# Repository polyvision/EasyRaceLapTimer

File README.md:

# EasyRaceLapTimer

EasyRaceLapTimer is a complete open source lap time tracker all-in-one solution for FPV racing quads. It supports an infrared based tracker solution which is completly open hardware and a VTX solution

What you get with EasyRaceLapTimer:

**Features:**

* host system for tracking the laps
* VTX sensoring
* IR transponders (code & schematic files for building them) with a transmitting range of 2 to 4 meters
* 63 available transponder IDs when using the project transponders
* changing the ID via a push button on the transponder, no additional programming required (started with version 0.3.1 of the transponders)
* update transponders with new code (Arduino hardware needed)
* setup guide for building your Raspberry PI host station
* the host station is also a WiFi access point to change configs etc on the fly
* monitoring mode, you can watch the stats with your mobile phones
* add your own team logo to the monitoring mode
* detailed stats about pilots and races
* sound effects for various events in a race
* TCP/IP and serial connections support for receiving lap times and commands from other time tracking systems
* export race events to PDF
* standard practice/ time trial mode
* competition mode for racing events with time penalties (satellites needed)
* automatic restarting of a race session after a specified idle time
* complete race management with heats & groups
* and much more comming soon

**Important notices**

EasyRaceLapTimer works basicly with any IR transponder, as long as you provide code for interpreting the IR pulses. Just have a look at the *ir_daemon* tool.

Be sure to use the full size of your SD card on the Raspberry PI

    sudo raspi-config

# Important information

The documentation for the project can be found in the [/docs](https://github.com/polyvision/EasyRaceLapTimer/tree/master/docs) directory.
There's also a huge [RCGroups](http://www.rcgroups.com/forums/showthread.php?t=2538917) thread with lots of answered questions, images etc.

# Version 0.6.x

You can download a SD card image for the PI of EasyRaceLapTimer on the following pages:

http://www.airbirds.de
http://www.easyracelaptimer.com

There's also an introduction video to the system.

# file structure

**/docs**
  documentation of nearly every part of the package

**/web**

the rails application

**/Arduino**

all arduino sketches

**/ir_daemon**

the cpp daemon for receiving the IR pulses

**/datasheets**

schematic files and more for transponders etc.

# Installation

fetch the source via git with the following command

    git clone git@github.com:polyvision/EasyRaceLapTimer.git

more details of each indivial package can be found in the *docs* folder

# Contributors
 * [Peter Provost](https://github.com/PProvost)
 * [Peisel](https://github.com/peisel)
 * [p3root](https://github.com/p3root)
 * [Sven Michel](https://github.com/svenmichel)
 * [bilson](https://github.com/bilson)
 
 and many more ! just add yourself if you contributed!

# license

The complete project uses the [GPL V3 license](http://www.gnu.org/licenses/gpl-3.0.de.html)

**development and sponsoring by [AirBirds](http://www.airbirds.de)**

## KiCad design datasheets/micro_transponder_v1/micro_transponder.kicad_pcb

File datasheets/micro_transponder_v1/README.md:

This is a transponder intended for indoor microdrones. It's not that bright, 
which is fine when flying only a few feet from the receiver. It's also very 
small, which is good when every milligram counts.

It can still be programmed using alligator clips on the sides. The lettering 
on the back will show you which pad goes where (PB0, PB1, etc.). See the 
ATtiny85 datasheet for how they connect to the physical pins and their 
extended features.

Solder the +5V and GND pads to the power. If necessary, a +3.7V input (such as 
from a 1S lipo cell) should be enough.

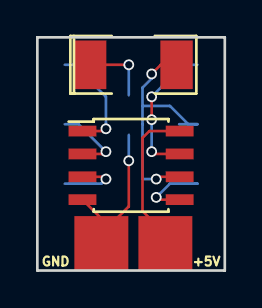
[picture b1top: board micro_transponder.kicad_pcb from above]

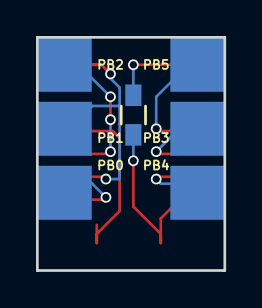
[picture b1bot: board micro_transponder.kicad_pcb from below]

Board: 2 copper layers, 10.4 x 13.0 mm, 9 parts (7 on the bottom side), 8 nets.

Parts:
D1: LED; SMD-2010_Pol
IC1: ATTINY85-S; SOIC-8_3.9x4.9mm_Pitch1.27mm
P1, P2, P3, P4, P5, P6: CONN_01X01; Measurement_Point_Square-SMD-Pad_Big
R1: 150 Ohm, 0.25W; R_0603_HandSoldering

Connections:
GND: IC1.4, R1.2
unnamed: D1.1, R1.1
unnamed: D1.2, IC1.6, P2.1
unnamed: IC1.1, P6.1
unnamed: IC1.2, P4.1
unnamed: IC1.3, P5.1
unnamed: IC1.5, P1.1
unnamed: IC1.7, P3.1

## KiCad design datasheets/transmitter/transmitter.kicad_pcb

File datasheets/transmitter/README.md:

**IMPORTANT**: This circuit changes the ATtiny85 output to pin 2, instead of pin 6. Be sure 
to change the program accordingly.  This makes room for the AVR ISP to attach without any 
overlapping pins.

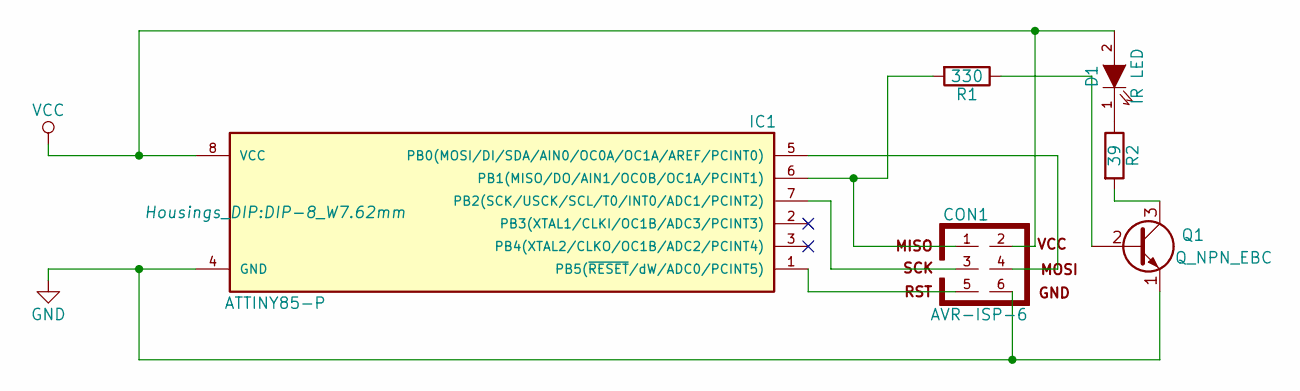
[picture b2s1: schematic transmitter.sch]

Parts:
CON1: AVR-ISP-6; Pin_Header_Straight_2x03
D1: IR LED; Pin_Header_Straight_1x02
IC1: ATTINY85-P; DIP-8_W7.62mm
Q1: Q_NPN_EBC; TO-92_Inline_Narrow_Oval
R1: 330; Resistor_Horizontal_RM7mm
R2: 39; Resistor_Horizontal_RM7mm

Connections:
GND: CON1.6, IC1.4 (GND), Q1.1 (E)
unnamed: CON1.1, IC1.6 (PB1(MISO/DO/AIN1/OC0B/OC1A/PCINT1)), R1.2
unnamed: CON1.3, IC1.7 (PB2(SCK/USCK/SCL/T0/INT0/ADC1/PCINT2))
unnamed: CON1.4, IC1.5 (PB0(MOSI/DI/SDA/AIN0/OC0A/OC1A/AREF/PCI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)
unnamed: CON1.5, IC1.1 (PB5(~RESET~/dW/ADC0/PCINT5))
unnamed: D1.1 (K), R2.1
unnamed: Q1.2 (B), R1.1
unnamed: Q1.3 (C), R2.2
VCC: CON1.2, D1.2 (A), IC1.8 (VCC)

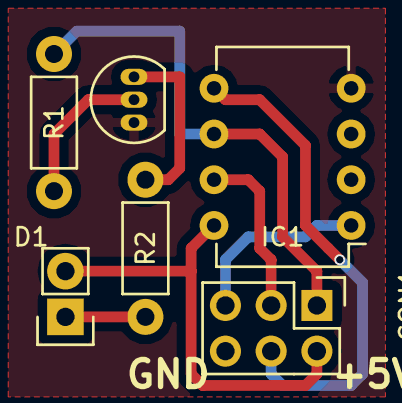
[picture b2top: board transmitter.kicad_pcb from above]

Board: 2 copper layers, 6 parts (0 on the bottom side), 9 nets.

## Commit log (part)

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2015-11-03 first working version of receiver
2015-11-04 new file strucure
2015-11-04 added some docs
2015-11-06 updated docs
2015-11-08 3 sensor support added buzzer support
2015-11-08 added gpio wiring for raspberry2
2015-11-09 added hardware.md
2015-11-10 added missing part
2015-11-13 added database config for production mode
2015-11-13 added pilots views, bugfixes
2015-11-13 fixes
2015-11-13 websockets r now configurable via env variable RAILS_CABLE_IP
2015-11-13 added init.d script
2015-11-14 added new style, added check for too fast lap
2015-11-16 preparing first stable release
2015-11-17 changed ir_daemon to 9 bit mode POST requests in seperate threads
2015-11-17 added Arduino files for the new 9bit transponder docs updated etc
2015-11-18 added missing transponder setup file
2015-11-18 added blog post link
2015-11-19 added soundfile configuration
2015-11-19 changed checksum calculation according to the documentation
2015-11-19 changed checksum calculation -> added new Transponder code v0.2
2015-11-20 better documentation
2015-11-20 updated documentation
2015-11-20 fixed a bug in displaying last rounds wrong time
2015-11-23 added api testing new config value lap_max_lap_time_in_seconds
2015-11-23 added database cleaner gem
2015-11-23 added button support on PIN 14 to start a new race started to clean up ir_daemon code
2015-11-24 rewrite of ir_daemon to support additionaly TCP/IP and serial connections
2015-11-24 Update setup_guide.md
    Made a bunch of edits and clarifications to help new users.
2015-11-26 added file
2015-11-27 better ui
2015-11-27 upcomming v0.3 added sensor case for different direction started to write update instructions, not complete yet
2015-11-30 wip competition mode
2015-12-01 first working version of the competition mode
2015-12-02 displayotron 3000 HAT server
2015-12-02 added lcd support (Displayotron 3000 HAT) support by adding an info server added more config switches to the ir_daemon
2015-12-04 beginning of satellite mode and time penalties for competition mode
2015-12-06 fixed competition mode ranking beginning of pdf generation
2015-12-06 add arch-linux description
2015-12-07 fixed a bug with double using transponder tokens
2015-12-07 satellite mode for the ir_daemon
2015-12-08 various bug fixes
2015-12-10 added version info the gui fixex image bug in pdf export
2015-12-10 - refactoring - added logging class for syslog and console logging (file is todo) - possibility to add more ir sensors via config file
2015-12-10 removed readme file
2015-12-10 updated testing code for Arduino Nano
2015-12-18 monitor view updates all 2 seconds removed actioncable
2015-12-18 changed config values
2015-12-18 first implementation of hot seat mode
2015-12-19 fixed spelling
2015-12-19 fixed a bug regarding hot seat mode in competition mode added spec for hot seat mode
2015-12-21 added udp broadcast, first tests
2015-12-22 fixes for upcomming v0.4b2
2015-12-22 fix for button visibility
2015-12-22 button visibility
2015-12-23 fixed typos and updated docs
2015-12-24 personal best lap time sfx
2015-12-24 fix for resetting the ir_daemon
2015-12-25 added sidekiq for background processing
2015-12-25 Use existing INI file and settings if exists
2016-01-04 test
2016-01-05 new colors new feeling more racy
2016-01-06 css fix
2016-01-11 working volume control
2016-01-11 playing custom sound files from via race director
2016-01-17 first working version of race director in the web gui improved some things and fixed a couple of bugs in ir_daemon
2016-01-17 fixes regarding logging
2016-01-22 fixed bug with creating a race session
2016-01-26 wip...
2016-01-29 play sound files for each lap in competition mode
2016-01-30 working playing lap num sound for a pilot in standard racing mode
2016-01-31 work in progress for sound effects during a race
2016-01-31 added docs notice
2016-02-01 working auto restart, option is called idle_time_in_seconds... let's test this on the field
2016-02-01 fixed a logic bomb ;)
2016-02-01 updated doc
2016-02-08 make the datasheet path a clickable link
2016-02-14 Kicad transmitter circuit and PCB
2016-02-16 Revert "Kicad PCB layout"
    This reverts commit 9afb40ae9a6d2ea0d6b4d8b9758429dc2c52fee4.
2016-02-16 Revert "Kicad transmitter circuit and PCB"
    This reverts commit 51ba06ca087ca7753eddb7d80b7d77b9e4b8eb6c.
2016-02-17 Add wiringpi to the list of required packages before building ir_daemon
2016-02-28 logo fix
2016-03-03 changed versioning
2016-03-05 IR Daemon v2 initial commit
2016-03-06 added transmitter code rev 0.3.1
2016-03-06 added rake task
2016-03-08 Convert to IO::Async
2016-03-10 Filter duplicate codes sent in short timespan
2016-03-13 Add header pulse/space of 1200 microseconds
2016-03-13 Switch for going between v0.3 (or lower) protocol or the newer version
2016-03-13 Correct handling of the checksum
2016-03-13 Document v.4 protocol, and move old protocol docs into an old file
2016-03-13 Correct note about clock rate
2016-03-15 IR sensor mount
    Alternative 3D printed IR receiver mount for TSOP31238. These are designed to mounted to the back side of agate with 1/4" or 5-6mm wide zip ties. The TSOP is held in the mount with double sided foam 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
2016-03-15 PCB Files for SMD Transponder and Pi Hat Base Station
2016-03-17 Add documentation
2016-03-18 [Invalidate Lap] Add "Invalidated" field and handle it in queries
2016-03-18 [Invalidate Lap] Basic UI to mark laps as invalid
2016-03-22 Send lap time to web server
2016-03-31 Reroute LED and transistor. Remove backup files from git.
2016-04-01 Adding screenshot of Pi Hat Base Station schematic
2016-04-06 Replace 3 blink startup with transponder id
    replace the 3 blink startup with two sets of blinks (with a blink in between) to display the MSB and LSB of the transponder ID. for example 21 will be displayed as 2 quick blinks, a separating blink,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
2016-04-09 fix bug with trasponder id flash on setup hanging
2016-04-09 flash transponder id each time trasponder id is changed
2016-04-12 Editing component list
    Added TSUS5202 as additional example of IR LED
    Changed 56 Ohm resistor to 33 Ohm for increased LED output.
    Added Edimax EW-7811Un as example USB WiFi adapter
2016-04-15 Fixed broken link for Transponder 0.3.1 schematic
2016-04-15 Add -bak to list of ignored files to catch a few kicad backup files
2016-04-29 Script to set transponder code via avrdude
2016-05-03 fixed specs
2016-05-04 incorrect pulses
    3rd bit should be a pulse rather than a space
2016-05-06 Updated setup_guide.md Added instructions to connect to the website
2016-05-09 Fixed typo in setup_guide.md "chmod +x" was missing a space
2016-05-12 Removed duplicate redis-server in apt-get command
2016-05-18 interface_guide.md v0.1
    A small guide for the ERLT interface
2016-05-20 Troubleshooting sidekiq startup
    Added section for troubleshooting issues with sidekiq not running on boot.
2016-05-20 Formatting changes
    Formatted the `code` sections of troubleshooting sound effects playback
2016-05-20 Cleaning up formatting
    I screwed up the code formatting and the back-ticks were visible.
2016-05-20 updated documentation
    added missing space in wkhtmltopdf permission set command
2016-06-02 first version with VTX sensoring support
2016-07-12 added missing brackets
2016-07-12 to clone the 0.6 branch
2016-08-01 migrated to rails 5, removed sqlite and switched to mysql as a database engine
2016-08-02 continued working on race events
2016-08-04 worked on basic race event flow starting race sessions via race event group, works ;)
2016-08-04 added ruby version file
2016-08-04 adjusted ruby version
2016-08-04 fixed tests,
    at present, spec/adapters/race_event_race_session_builder_adapter_spec.rb works runned alone, with all other tests together not... but why?
2016-08-05 added mode for regrouping a heat based on previous heat pilot placements
2016-08-05 improvements for race event managent in the GUI
2016-08-07 added the possibility to move pilots from one group to another
2016-08-08 fixed a bug in next heat calculation
2016-08-24 added pilot json data to monitor api
2016-08-24 beginning of ir_daemon2 based on nodejs thanks to Rodrigo Pérez for the base code of the vtx sensor
2016-08-25 added import of pilots from fpv-sports.io y:
2016-08-25 added validation & invalidation to history
2016-08-30 added possibility to merge lap times of a pilot
2016-08-31 added support for the RaceBox (upcomming Raspbery PI OpenSource HAT) for easier connecting the PocketEdition and other VTX systems
2016-08-31 removed monitor polling in favour of actioncable (websockets)
2016-09-01 improved information
2016-09-02 added actioncable to race box config
2016-09-02 updated docs, small fixes
2016-09-05 first working implementation with fpv-sports.io support
2016-09-07 added invalidating laps in monitor
2016-09-07 a few more changes
2016-09-29 fix for getting data from fpv-sports.io
2016-09-29 wip ir decoding via nodejs
2017-03-23 Update wifi.md
    The password in the Setup Guide differs from the original password here. Updating it to reduce confusion.
2017-07-30 fixes missing url
2017-07-30 adds mac friendly tool to docs
2017-07-31 fix lap_track response on standard mode
2021-02-18 Updated to rails 4.2.11.3 to run on modern systems
2021-02-25 Updated dependencies
2021-02-27 Updated webpack output
2021-02-28 Bump superagent from 1.8.5 to 3.7.0 in /web
    Bumps [superagent](https://github.com/visionmedia/superagent) from 1.8.5 to 3.7.0.
    - [Release notes](https://github.com/visionmedia/superagent/releases)
    - [Changelog](https://github.com/visionmedia/superagent/blob/master/HISTORY.md)
    - [Commits](https://github.com/visionmedia/superagent/commits/v3.7.0)
2021-02-28 Bump node-fetch from 1.7.3 to 2.6.1 in /web
    Bumps [node-fetch](https://github.com/bitinn/node-fetch) from 1.7.3 to 2.6.1.
    - [Release notes](https://github.com/bitinn/node-fetch/releases)
    - [Changelog](https://github.com/node-fetch/node-fetch/blob/master/docs/CHANGELOG.md)
    - [Commits](https://github.com/bitinn/node-fetch/compare/1.7.3...v2.6.1)
2021-05-12 Bump lodash from 3.10.1 to 4.17.21 in /web
    Bumps [lodash](https://github.com/lodash/lodash) from 3.10.1 to 4.17.21.
    - [Release notes](https://github.com/lodash/lodash/releases)
    - [Commits](https://github.com/lodash/lodash/compare/3.10.1...4.17.21)
2022-01-22 Bump node-fetch from 1.7.3 to 3.1.1 in /web
    Bumps [node-fetch](https://github.com/node-fetch/node-fetch) from 1.7.3 to 3.1.1.
    - [Release notes](https://github.com/node-fetch/node-fetch/releases)
    - [Changelog](https://github.com/node-fetch/node-fetch/blob/main/docs/CHANGELOG.md)
    - [Commits](https://github.com/node-fetch/node-fetch/compare/1.7.3...v3.1.1)
    ---
    updated-dependencies:
2022-11-01 Bump minimatch and babel-loader in /web
    Bumps [minimatch](https://github.com/isaacs/minimatch) to 3.1.2 and updates ancestor dependency [babel-loader](https://github.com/babel/babel-loader). These dependencies need to be updated together.
    Updates `minimatch` from 2.0.10 to 3.1.2
    - [Release notes](https://github.com/isaacs/minimatch/releases)
    - [Commits](https://github.com/isaacs/minimatch/compare/v2.0.10...v3.1.2)
    Updates `babel-loader` from 5.4.2 to 9.0.1
    - [Release notes](https://github.com/babel/babel-loader/releases)
2022-12-06 Bump qs and superagent in /web
    Bumps [qs](https://github.com/ljharb/qs) to 6.11.0 and updates ancestor dependency [superagent](https://github.com/ladjs/superagent). These dependencies need to be updated together.
    Updates `qs` from 2.3.3 to 6.11.0
    - [Release notes](https://github.com/ljharb/qs/releases)
    - [Changelog](https://github.com/ljharb/qs/blob/main/CHANGELOG.md)
    - [Commits](https://github.com/ljharb/qs/compare/v2.3.3...v6.11.0)
    Updates `superagent` from 1.8.5 to 8.0.5
